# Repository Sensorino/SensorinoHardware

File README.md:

SensorinoHardware
=================

Hardware design of the Sensorino board

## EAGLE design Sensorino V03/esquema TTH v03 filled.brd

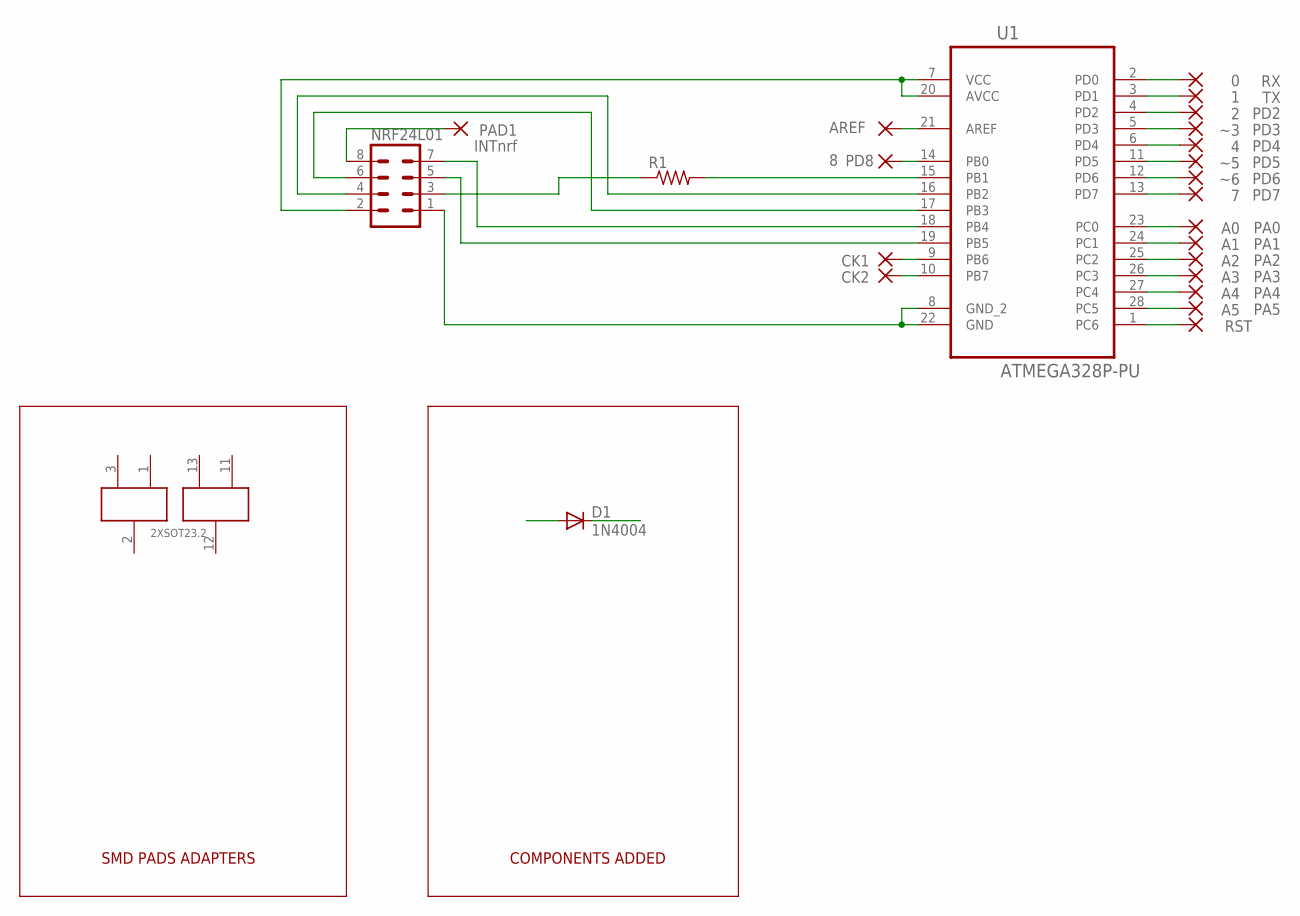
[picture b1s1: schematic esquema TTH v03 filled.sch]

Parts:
2: PD2; 2,15/1,0
4: PD4; 2,15/1,0
7: PD7; 2,15/1,0
8: PD8; 2,15/1,0
A0: PA0; 2,15/1,0
A1: PA1; 2,15/1,0
A2: PA2; 2,15/1,0
A3: PA3; 2,15/1,0
A4: PA4; 2,15/1,0
A5: PA5; 2,15/1,0
AREF: 2,15/1,0
CK1, CK2: 2,15/1,0
D1: 1N4004; DO41-10
NRF24L01: MA04-2
PAD1: INTnrf; 2,15/1,0
R1: R-US_0207/10; 0207/10
RST: 2,15/1,0
RX: 0; 2,15/1,0
TX: 1; 2,15/1,0
U1: ATMEGA328P-PU; DIP254P762X457-28
U$2: 2XSOT23.2; SOT23.5
~3: PD3; 2,15/1,0
~5: PD5; 2,15/1,0
~6: PD6; 2,15/1,0

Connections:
unnamed: NRF24L01.4, U1.16 (PB2)
unnamed: NRF24L01.8, PAD1.1
unnamed: NRF24L01.6, U1.17 (PB3)
unnamed: NRF24L01.3, R1.1
unnamed: NRF24L01.5, U1.19 (PB5)
unnamed: R1.2, U1.15 (PB1)
unnamed: CK2.1, U1.10 (PB7)
unnamed: CK1.1, U1.9 (PB6)
unnamed: AREF.1, U1.21 (AREF)
unnamed: 8.1, U1.14 (PB0)
unnamed: RX.1, U1.2 (PD0)
unnamed: TX.1, U1.3 (PD1)
unnamed: 2.1, U1.4 (PD2)
unnamed: U1.5 (PD3), ~3.1
unnamed: 4.1, U1.6 (PD4)
unnamed: U1.11 (PD5), ~5.1
unnamed: U1.12 (PD6), ~6.1
unnamed: 7.1, U1.13 (PD7)
unnamed: A0.1, U1.23 (PC0)
unnamed: A1.1, U1.24 (PC1)
unnamed: A2.1, U1.25 (PC2)
unnamed: A3.1, U1.26 (PC3)
unnamed: A4.1, U1.27 (PC4)
unnamed: A5.1, U1.28 (PC5)
unnamed: RST.1, U1.1 (PC6)
unnamed: NRF24L01.7, U1.18 (PB4)
unnamed: NRF24L01.2, U1.7 (VCC), U1.20 (AVCC)
unnamed: NRF24L01.1, U1.8 (GND_2), U1.22 (GND)

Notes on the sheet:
SMD PADS ADAPTERS
COMPONENTS ADDED

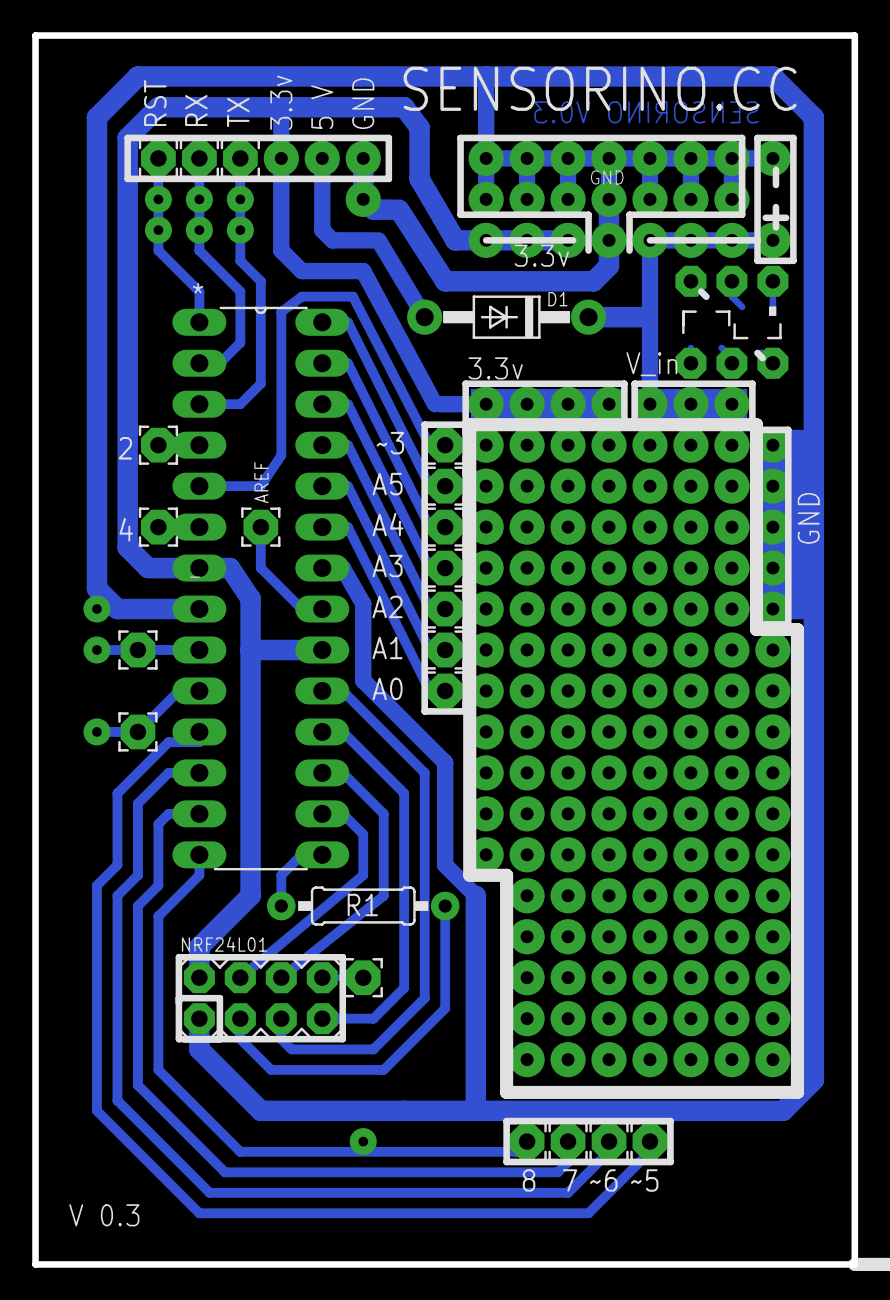
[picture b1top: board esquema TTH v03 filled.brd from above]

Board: 2 copper layers, 50.8 x 76.2 mm, 25 parts (0 on the bottom side), 28 nets.

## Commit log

2014-08-19 Sensorino pcb version v03 working
